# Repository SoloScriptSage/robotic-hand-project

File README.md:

# 🤖 Robotic Hand Project

A wireless gesture-controlled robotic hand built with Arduino, flex sensors, and NRF24L01 radio modules. A glove fitted with flex sensors captures hand movements and transmits them wirelessly to a 3D-printed robotic hand, which mirrors the gestures in real time via servo motors.

Originally developed as an open-source prosthetic research platform.

---

## 📸 Demo

---

## ✨ Features

- Real-time wireless gesture control via NRF24L01 (250KBPS, ~100m range)
- 5-finger articulation using MG996R servo motors
- Flex sensor glove for intuitive hand tracking
- Per-finger calibration support
- Simple, hackable codebase — easy to extend

---

## 📁 Repository Structure

```
robotic-hand-project/
│
├── firmware/
│   ├── transmitter/        ← glove Arduino code
│   ├── receiver/           ← hand Arduino code
│   ├── test_sensors/       ← flex sensor calibration helper
│   └── servo_test/         ← servo sweep test
│
├── hardware/
│   ├── schematics/         ← wiring diagrams
│   ├── pcb/                ← PCB files
│   ├── mechanical/
│   │   └── robotic-hand-stls/  ← 3D print files
│   ├── assembly-guides/    ← step by step assembly
│   ├── datasheets/         ← component datasheets
│   └── BOM.md              ← full bill of materials
│
├── docs/
│   ├── calibration.md      ← flex sensor calibration guide
│   └── troubleshooting.md  ← common issues and fixes
│
├── images/                 ← photos and demo gifs
├── .gitignore
├── LICENSE
└── README.md
```

---

## 🛠️ Materials

Full bill of materials with component links and prices → [`hardware/BOM.md`](hardware/BOM.md)

---

## 🗺️ Schematics

Wiring diagrams for both transmitter and receiver → [`hardware/schematics/`](hardware/schematics/)

> ⚠️ Power the NRF24L01 modules from the **3.3V pin only** — they are not 5V tolerant.

---

## 🖨️ 3D Model

The hand structure is sourced from [Viral Science](https://www.viralsciencecreativity.com/post/arduino-flex-sensor-controlled-robot-hand). Print files are available in [`hardware/mechanical/robotic-hand-stls/`](hardware/mechanical/robotic-hand-stls/).

Print settings:
- Material: PLA or PETG
- Infill: 20–30%
- Supports: Yes (for finger joints)

---

## ⚙️ Setup

### 1. Clone the repository
```bash
git clone https://github.com/SoloScriptSage/robotic-hand-project.git
```

### 2. Install Arduino libraries
In Arduino IDE go to **Sketch → Include Library → Manage Libraries** and install:
- `RF24` by TMRh20
- `Servo` (built-in)

### 3. Assemble the hardware
- Print and assemble the 3D hand following the guides in [`hardware/assembly-guides/`](hardware/assembly-guides/)
- Wire flex sensors to the glove according to the schematics
- Wire servos to the receiver board according to the schematics

### 4. Calibrate the flex sensors
Follow the step-by-step guide → [`docs/calibration.md`](docs/calibration.md)

### 5. Flash the firmware
- Flash [`firmware/transmitter/transmitter.ino`](firmware/transmitter/transmitter.ino) to the **glove Arduino**
- Flash [`firmware/receiver/receiver.ino`](firmware/receiver/receiver.ino) to the **hand Arduino**

### 6. Test
- Flash [`firmware/servo_test/servo_test.ino`](firmware/servo_test/servo_test.ino) to verify all servos sweep correctly
- Power both Arduinos and open Serial Monitor — you should see sensor values on the transmitter and matching received values on the receiver

---

## 💻 Code Overview

| File | Description |
|---|---|
| `transmitter.ino` | Reads flex sensors, maps to servo angles, transmits via NRF24L01 |
| `receiver.ino` | Receives data, writes angles to servo motors |
| `test_sensors.ino` | Prints raw flex sensor values for calibration |
| `servo_test.ino` | Sweeps all servos 0→180→0 for hardware testing |

---

## 🧪 Testing

---

## 📖 Docs

- [Calibration Guide](docs/calibration.md)
- [Troubleshooting](docs/troubleshooting.md)

---

## 🚀 Roadmap

- [ ] Per-finger calibration via Serial Monitor wizard
- [ ] Haptic feedback on glove (vibration motors)
- [ ] NRF24L01 external antenna for extended range
- [ ] Replace flex sensors with IMU-based gesture recognition
- [ ] Full prosthetic enclosure design
- [ ] Support for wrist rotation (6th servo)

---

## 🙏 Acknowledgments

- [Viral Science](https://www.viralsciencecreativity.com/post/arduino-flex-sensor-controlled-robot-hand) for the 3D hand model
- [TMRh20](https://github.com/nRF24/RF24) for the RF24 library
- The open-source Arduino community

---

## 📄 License

This project is open-source under the [MIT License](LICENSE).

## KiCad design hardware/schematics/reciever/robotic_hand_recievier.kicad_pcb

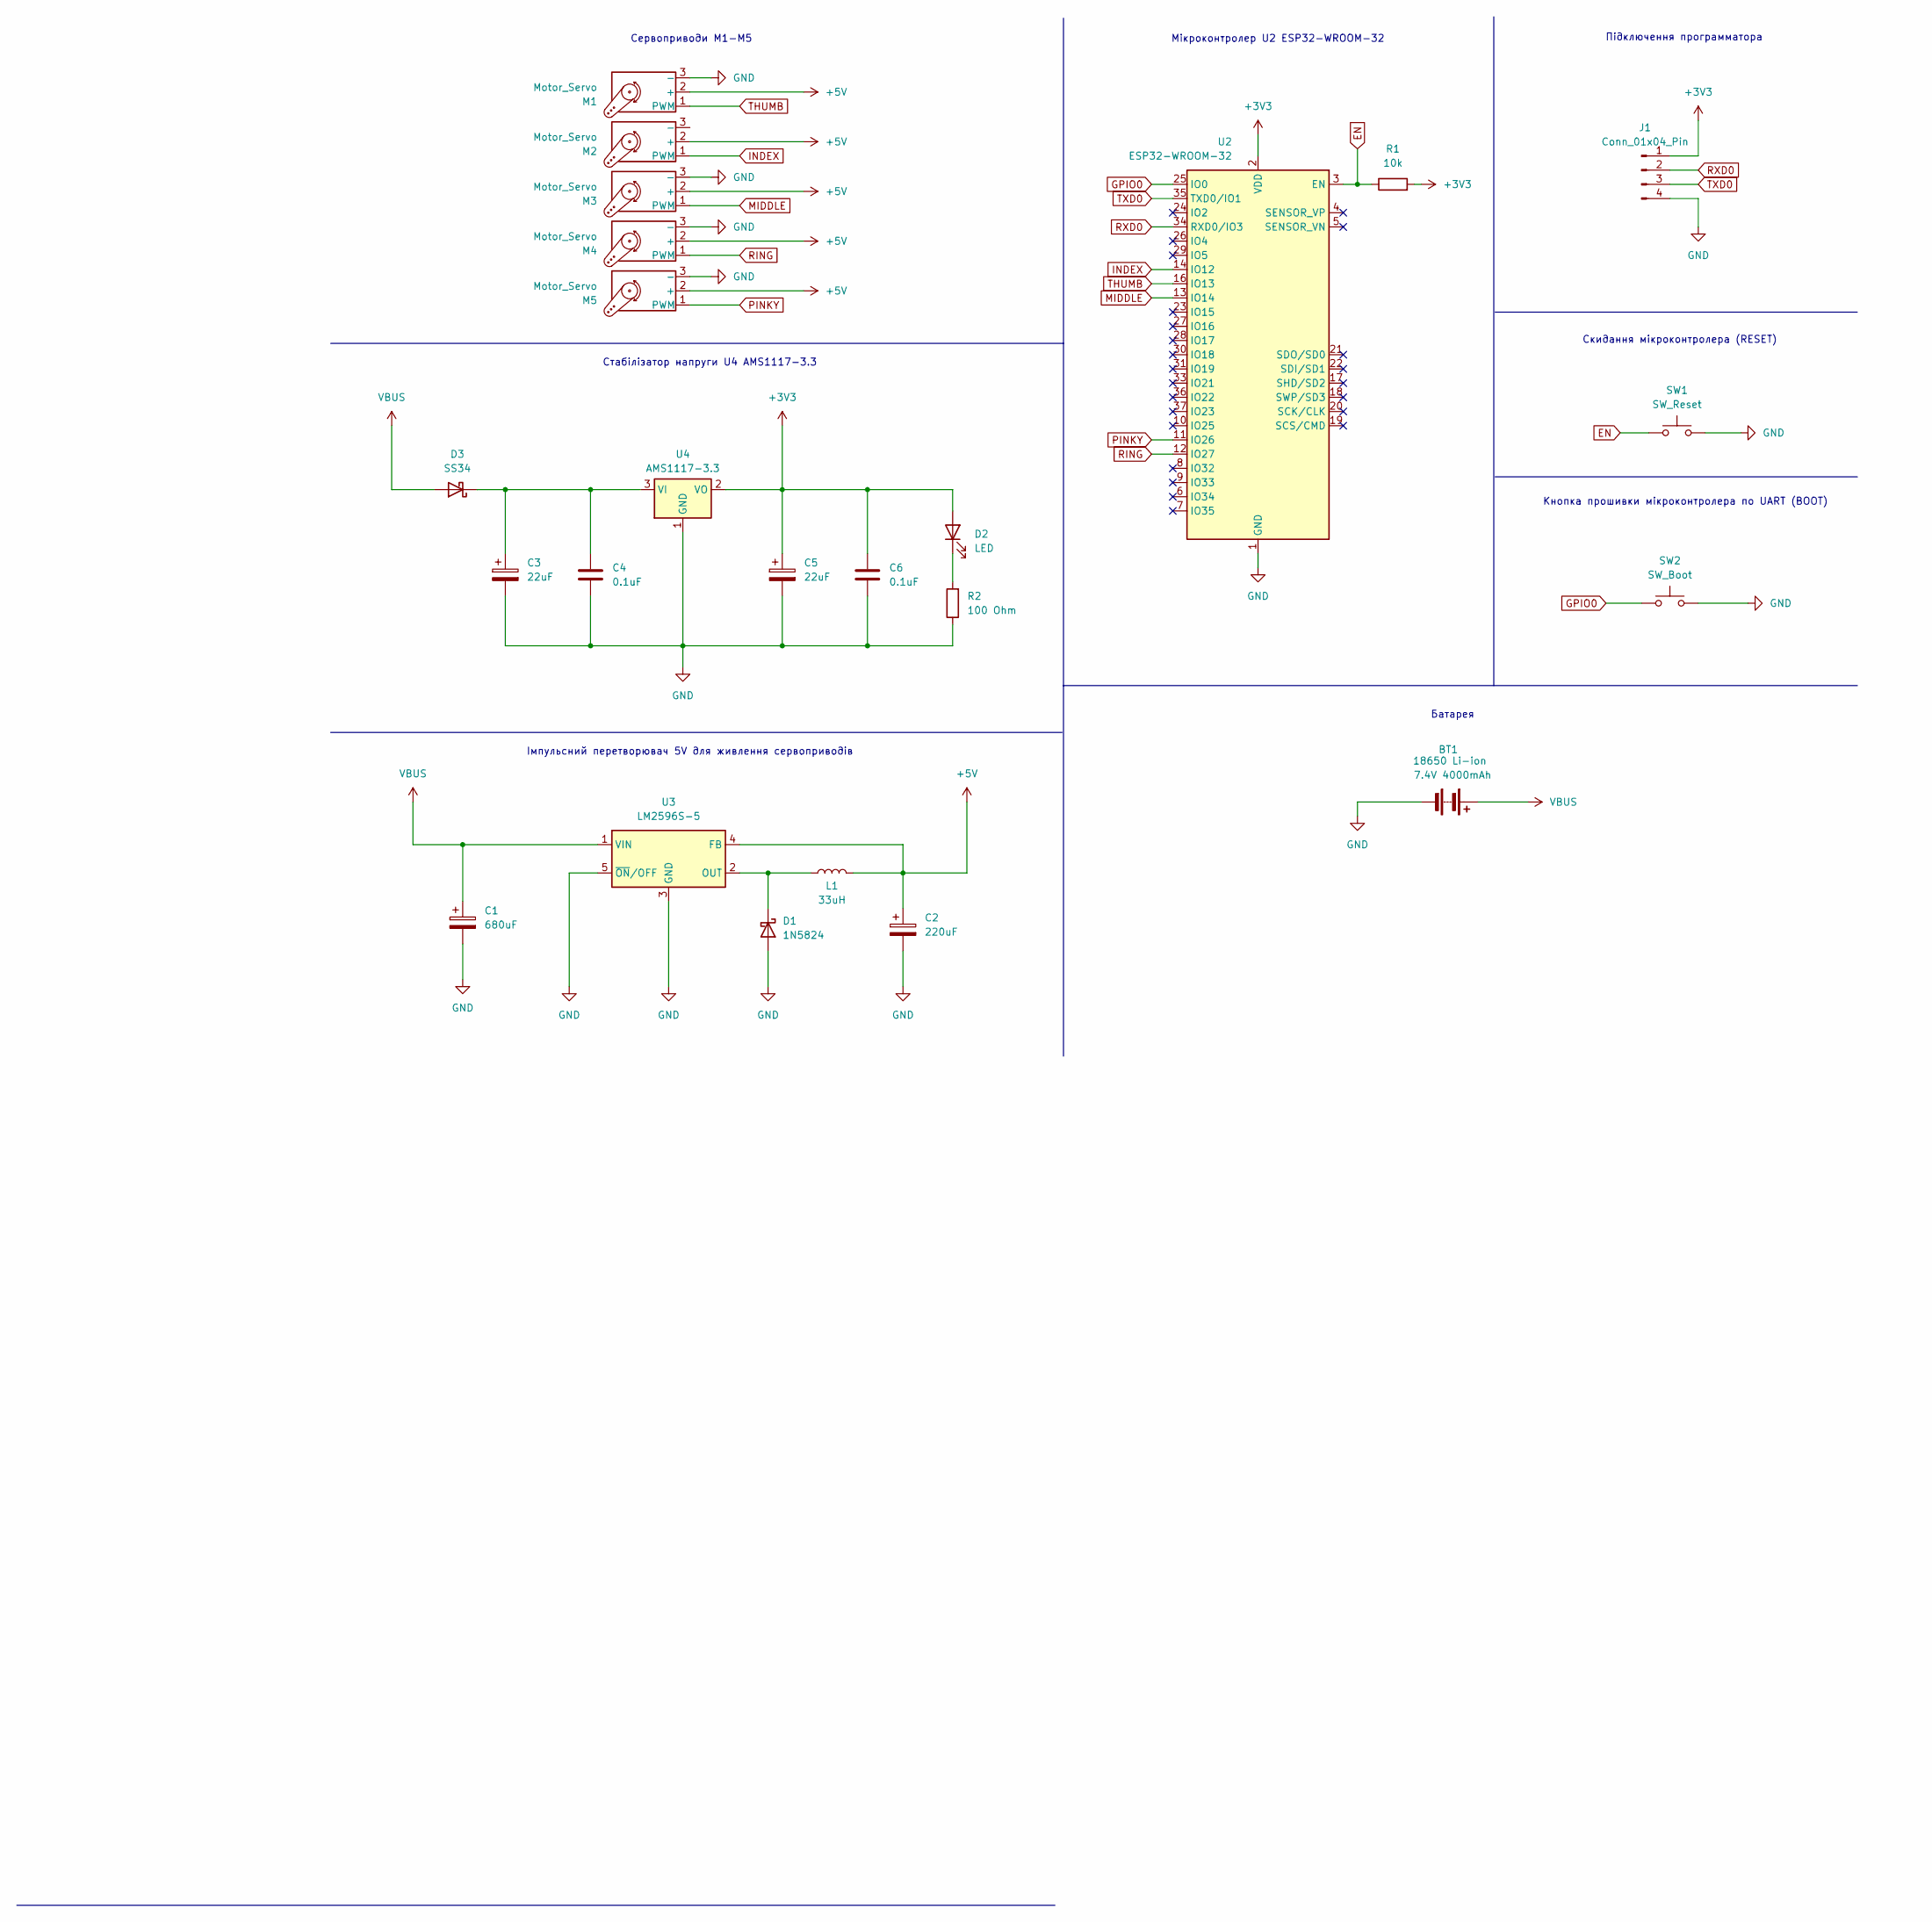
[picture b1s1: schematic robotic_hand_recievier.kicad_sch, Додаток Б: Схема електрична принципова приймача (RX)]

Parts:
BT1: 18650 Li-ion; 2X-BATTERY-HOLDER-18650
C1: 680uF; CP_Radial_D8.0mm_P3.50mm
C2: 220uF; CP_Radial_D8.0mm_P3.50mm
C3, C5: 22uF; C_1206_3216Metric
C4, C6: 0.1uF; C_0805_2012Metric
D1: 1N5824; D_SMB
D2: LED; LED_0805_2012Metric
D3: SS34; D_SMB
J1: Conn_01x04_Pin; PinHeader_1x04_P2.54mm_Vertical
L1: 33uH; L_Axial_L5.3mm_D2.2mm_P10.16mm_Horizontal_Vishay_IM-1
M1, M2, M3, M4, M5: Motor_Servo; PinHeader_1x03_P2.54mm_Vertical
R1: 10k; R_0805_2012Metric
R2: 100 Ohm; R_0805_2012Metric
SW1: SW_Reset; SW_SPST_B3U-1000P
SW2: SW_Boot; SW_SPST_B3U-1000P
U2: ESP32-WROOM-32
U3: LM2596S-5; TO-263-5_TabPin3
U4: AMS1117-3.3; SOT-223-3_TabPin2

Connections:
+3V3: C5.1, C6.1, D2.2 (A), J1.1, R1.2, U2.2 (VDD), U4.2 (VO)
+5V: C2.1, L1.2, M1.2 (+), M2.2 (+), M3.2 (+), M4.2 (+), M5.2 (+), U3.4 (FB)
EN: R1.1, SW1.1, U2.3 (EN); also elsewhere on the board
GND: BT1.2 (-), C1.2, C2.2, C3.2, C4.2, C5.2, C6.2, D1.2 (A), J1.4, M1.3 (-), M3.3 (-), M4.3 (-), M5.3 (-), R2.1, SW1.2, SW2.2, U2.1 (GND), U2.15 (GND), U2.38 (GND), U2.39 (GND), U3.3 (GND), U3.5 (~ON/OFF), U4.1 (GND); also elsewhere on the board
GPIO0: SW2.1, U2.25 (IO0); also elsewhere on the board
INDEX: M2.1 (PWM), U2.14 (IO12)
MIDDLE: M3.1 (PWM), U2.13 (IO14)
unnamed: D1.1 (K), L1.1, U3.2 (OUT)
unnamed: D2.1 (K), R2.2
unnamed: C3.1, C4.1, D3.1 (K), U4.3 (VI)
PINKY: M5.1 (PWM), U2.11 (IO26)
RING: M4.1 (PWM), U2.12 (IO27)
RXD0: J1.2, U2.34 (RXD0/IO3)
THUMB: M1.1 (PWM), U2.16 (IO13)
TXD0: J1.3, U2.35 (TXD0/IO1)
VBUS: BT1.1 (+), C1.1, D3.2 (A), U3.1 (VIN)

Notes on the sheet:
Сервоприводи M1-M5
Кнопка прошивки мікроконтролера по UART (BOOT)
Стабілізатор напруги U4 AMS1117-3.3
Підключення программатора
Батарея
Мікроконтролер U2 ESP32-WROOM-32
Імпульсний перетворювач 5V для живлення сервоприводів
Скидання мікроконтролера (RESET)

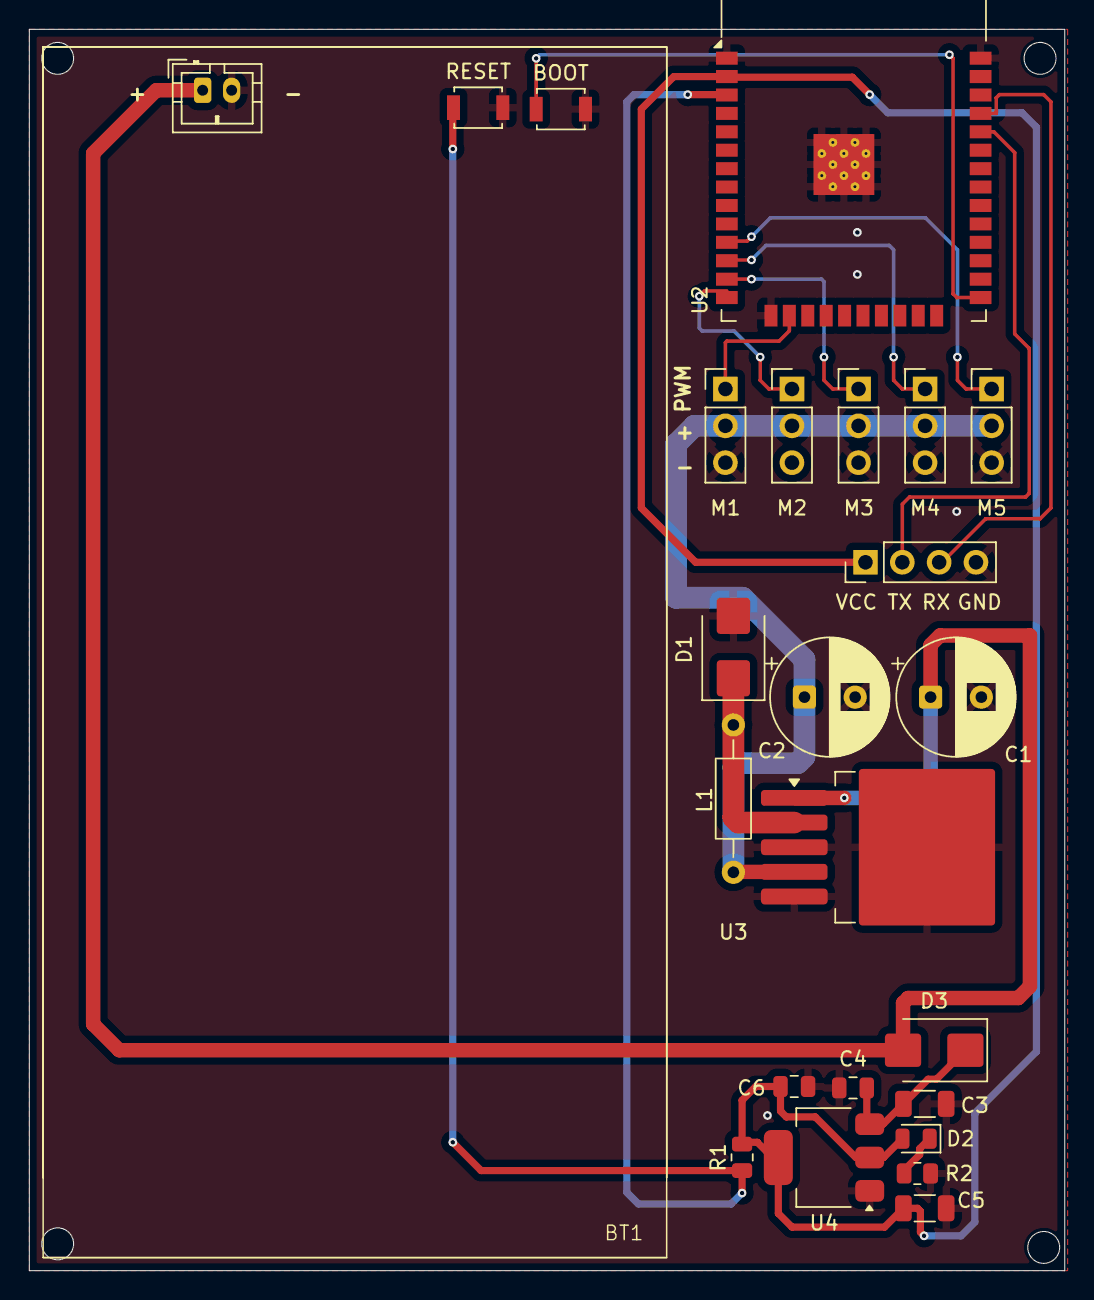
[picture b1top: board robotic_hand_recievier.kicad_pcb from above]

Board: 2 copper layers, 71.4 x 85.6 mm, 24 parts (0 on the bottom side), 16 nets.

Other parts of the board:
BOOT: SW_Boot; SW_SPST_B3U-1000P
RESET: SW_Reset; SW_SPST_B3U-1000P

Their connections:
EN: RESET.1; also elsewhere on the board
GND: BOOT.2, RESET.2; also elsewhere on the board
GPIO0: BOOT.1; also elsewhere on the board

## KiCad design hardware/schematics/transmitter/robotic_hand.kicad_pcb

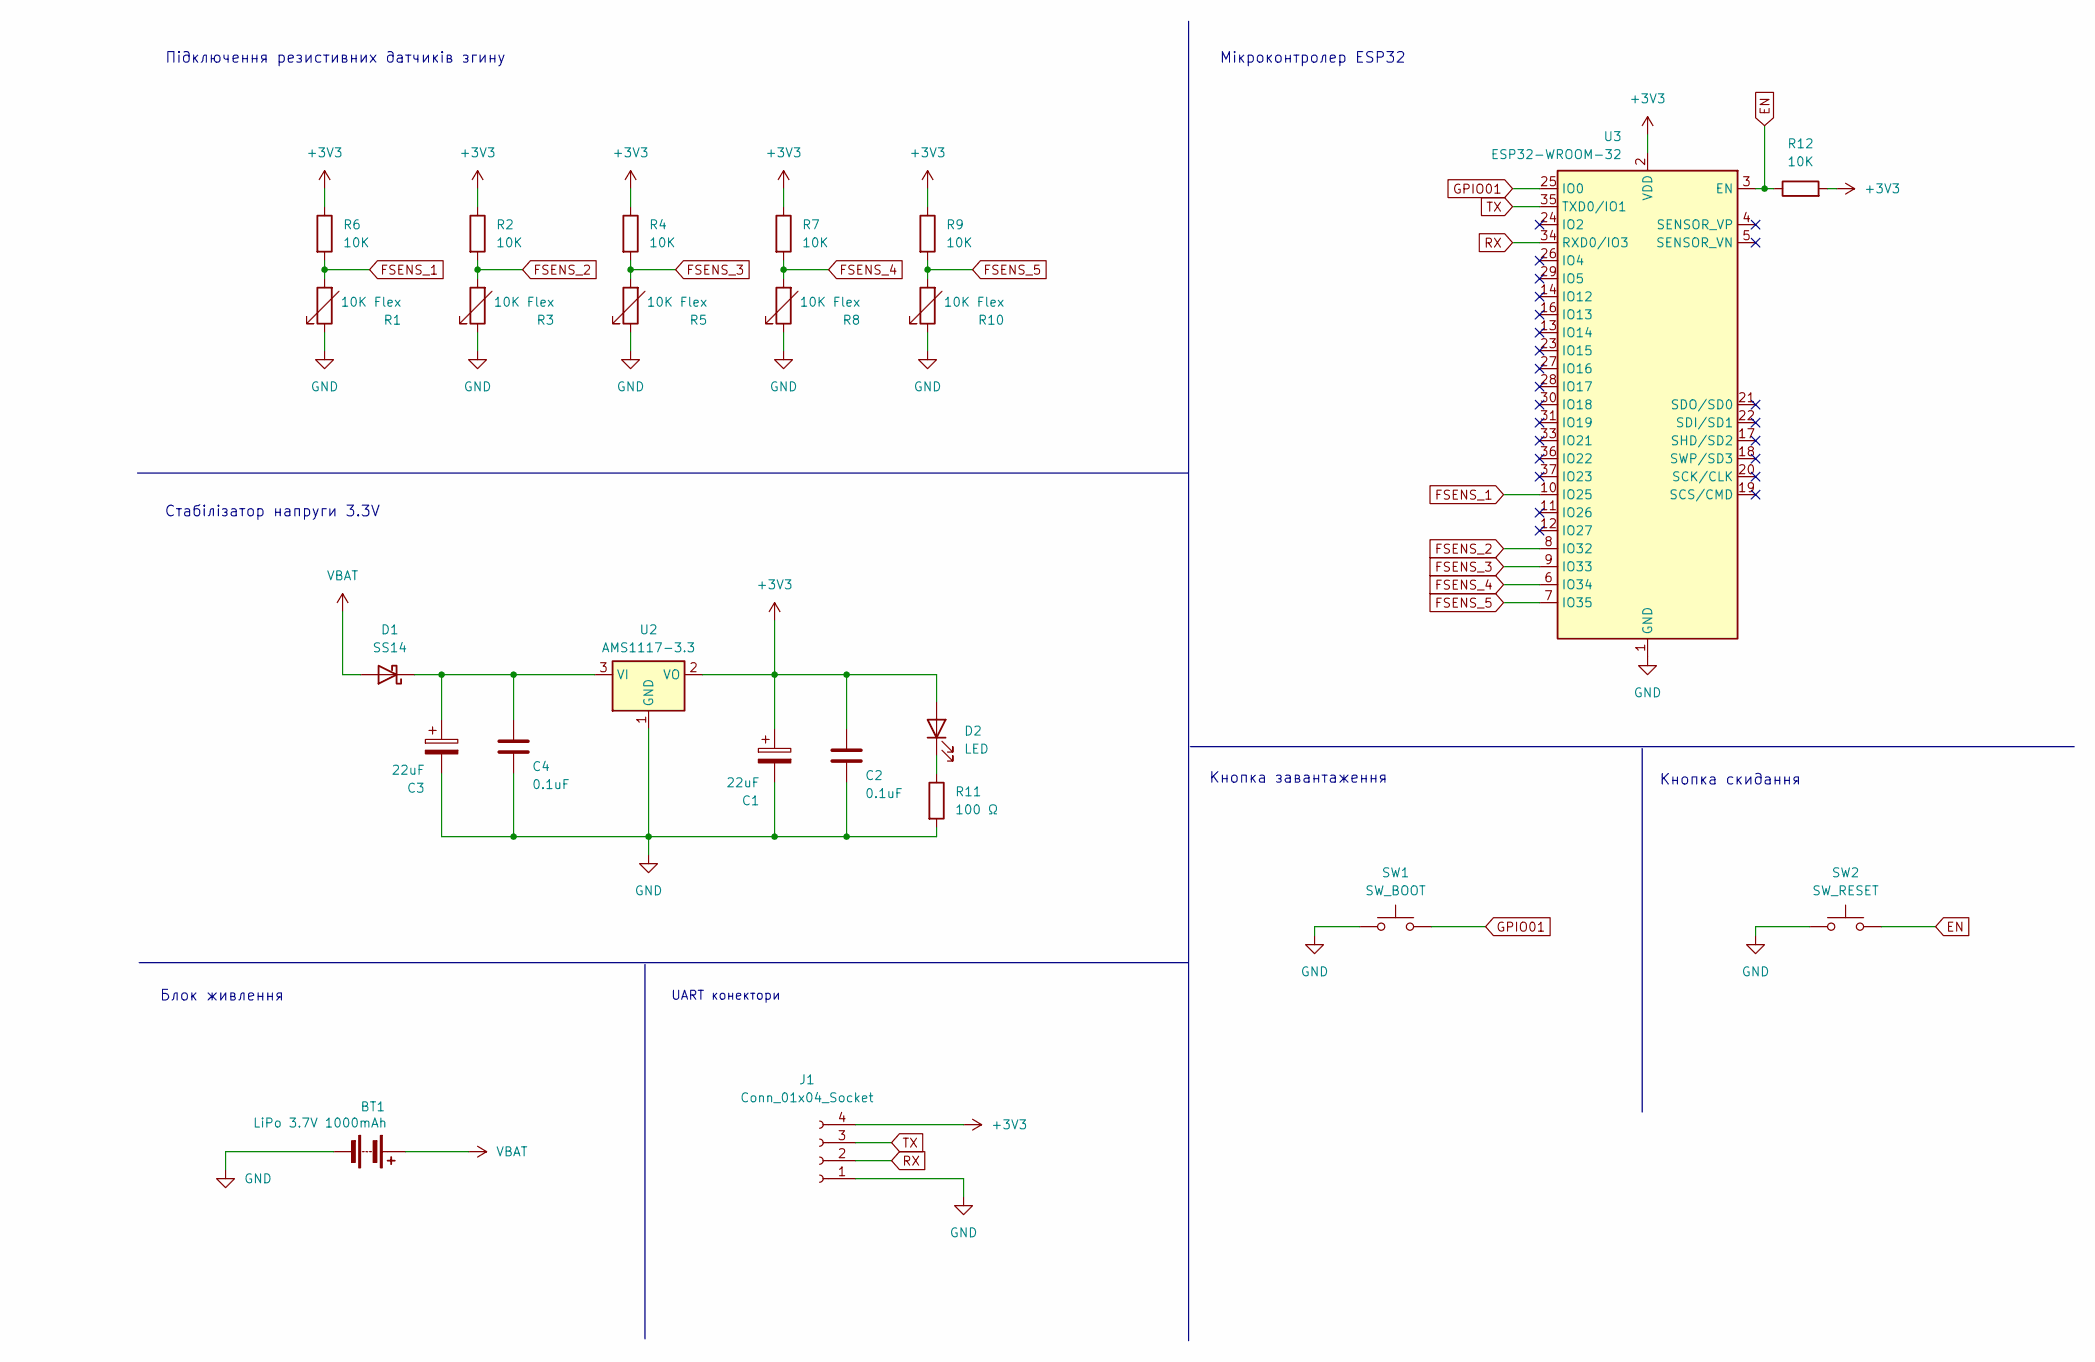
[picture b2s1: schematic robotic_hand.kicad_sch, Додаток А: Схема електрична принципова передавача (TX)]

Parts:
BT1: LiPo 3.7V 1000mAh; JST_PH_S2B-PH-K_1x02_P2.00mm_Horizontal
C1, C3: 22uF; C_1206_3216Metric
C2, C4: 0.1uF; C_0805_2012Metric
D1: SS14; D_SMA
D2: LED; LED_0805_2012Metric
J1: Conn_01x04_Socket; PinHeader_1x04_P2.54mm_Vertical
R1, R3, R5, R8, R10: 10K Flex; JST_PH_S2B-PH-K_1x02_P2.00mm_Horizontal
R2, R4, R6, R7, R9, R12: 10K; R_0805_2012Metric
R11: 100 Ω; R_0805_2012Metric
SW1: SW_BOOT; SW_SPST_B3U-1000P
SW2: SW_RESET; SW_SPST_B3U-1000P
U2: AMS1117-3.3; SOT-223-3_TabPin2
U3: ESP32-WROOM-32

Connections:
+3V3: C1.1, C2.2, D2.2 (A), J1.4, R2.1, R4.1, R6.1, R7.1, R9.1, R12.2, U2.2 (VO), U3.2 (VDD)
EN: R12.1, SW2.2, U3.3 (EN); also elsewhere on the board
FSENS_1: R1.2, R6.2, U3.10 (IO25)
FSENS_2: R2.2, R3.2, U3.8 (IO32)
FSENS_3: R4.2, R5.2, U3.9 (IO33)
FSENS_4: R7.2, R8.2, U3.6 (IO34)
FSENS_5: R9.2, R10.2, U3.7 (IO35)
GND: BT1.2 (-), C1.2, C2.1, C3.2, C4.1, J1.1, R1.1, R3.1, R5.1, R8.1, R10.1, R11.2, SW1.1, SW2.1, U2.1 (GND), U3.1 (GND), U3.15 (GND), U3.38 (GND), U3.39 (GND); also elsewhere on the board
GPIO01: SW1.2, U3.25 (IO0); also elsewhere on the board
unnamed: C3.1, C4.2, D1.1 (K), U2.3 (VI)
unnamed: D2.1 (K), R11.1
RX: J1.2, U3.34 (RXD0/IO3)
TX: J1.3, U3.35 (TXD0/IO1)
VBAT: BT1.1 (+), D1.2 (A)

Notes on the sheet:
Кнопка завантаження
Кнопка скидання
Блок живлення
Мікроконтролер ESP32
Підключення резистивних датчиків згину
UART конектори
Стабілізатор напруги 3.3V

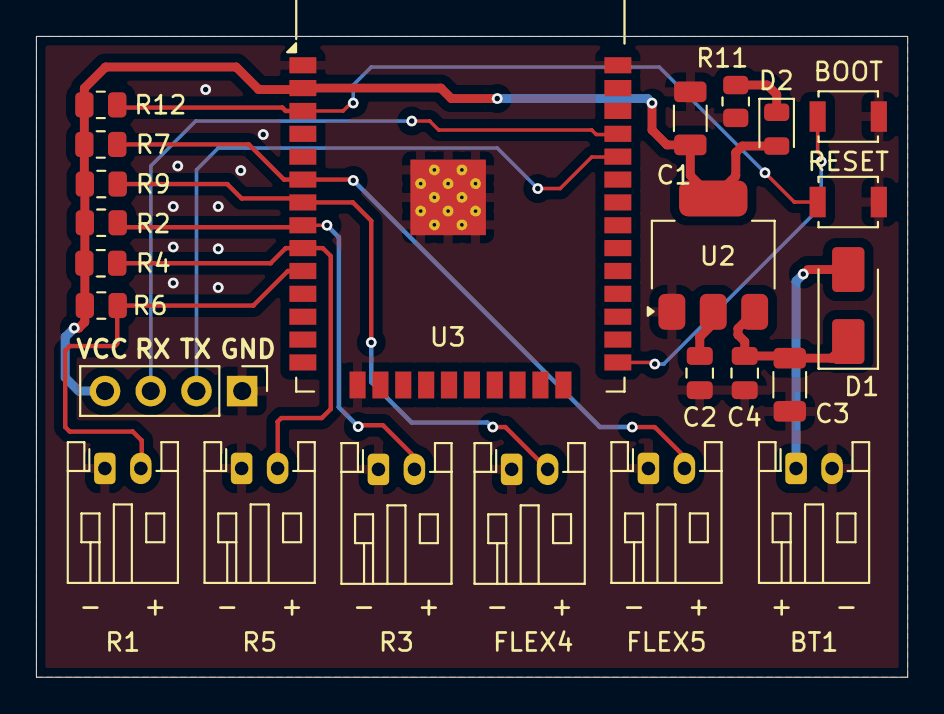
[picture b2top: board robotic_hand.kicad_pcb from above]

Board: 2 copper layers, 48.4 x 35.6 mm, 24 parts (0 on the bottom side), 14 nets.

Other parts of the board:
BOOT: SW_BOOT; SW_SPST_B3U-1000P
RESET: SW_RESET; SW_SPST_B3U-1000P

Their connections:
EN: RESET.2; also elsewhere on the board
GND: BOOT.1, RESET.1; also elsewhere on the board
GPIO01: BOOT.2; also elsewhere on the board

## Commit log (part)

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2025-06-09 Create myfile
2025-06-09 Create file
2025-06-09 Create new
2025-06-09 Create fi9le
2025-06-09 Rename hardware/schematics/robotic_hand_transmitter.pdf to hardware/schematics/transmitter/robotic_hand_transmitter.pdf
2025-06-09 Rename hardware/schematics/robotic_hand_recievier.pdf to hardware/schematics/reciever/robotic_hand_recievier.pdf
2025-06-09 Create some_pcbs
2025-06-09 Create bill_of_materials
2025-06-09 Create assembly-guides
2025-06-09 Create cad-models
2025-06-09 Create stls
2025-06-09 Rename firmware/src/reciever.ino to firmware/src/receiver/rx.ino
2025-06-09 Create electronics
2025-09-05 Rename BOM.md to dosc/BOM.md
2025-09-05 Rename BOM.md to BOM.md
2026-03-04 Refactor transmitter code for flex sensor handling
2026-03-04 Refactor receiver.ino for improved readability
2026-03-04 Refactor flex sensor readings to use array
    Refactored sensor reading code to use an array for flex pins.
2026-03-04 Simplify servo control using an array
    Refactored servo control to use an array for better scalability.
2026-03-04 Refine flex sensor values and radio settings
    Updated FLEX_MIN and FLEX_MAX values for better accuracy. Adjusted radio retry settings.
2026-03-04 Change radio retries from 0 to 3
2026-03-04 Create .gitignore for build artifacts and IDE files
    Add common ignore patterns for Arduino, IDE, and OS files.
2026-03-04 Add test_sensors.ino for sensor testing
2026-03-04 Rename servos_test.ino to servo_test.ino
2026-03-04 Revise README for clarity and additional details
    Updated project description, features, and setup instructions in README.md.
2026-03-04 Restructure repo: fix firmware, add BOM, calibration and troubleshooting docs, update README

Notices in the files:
hardware/schematics/transmitter/robotic_hand.kicad_pcb:
© 2026
